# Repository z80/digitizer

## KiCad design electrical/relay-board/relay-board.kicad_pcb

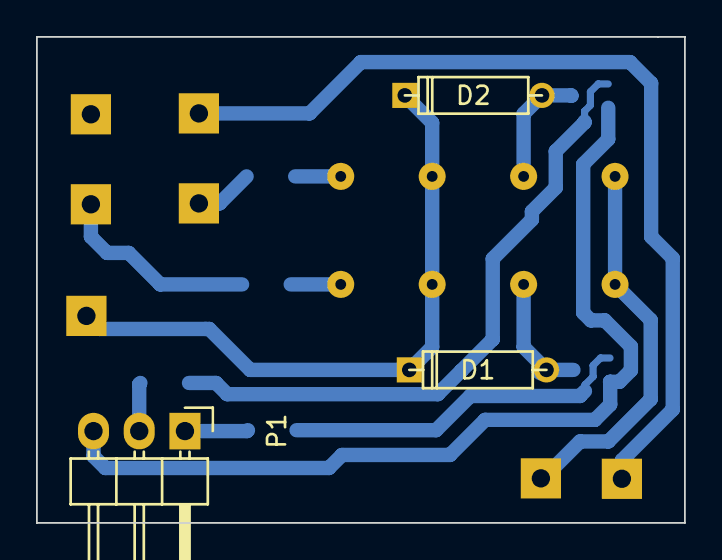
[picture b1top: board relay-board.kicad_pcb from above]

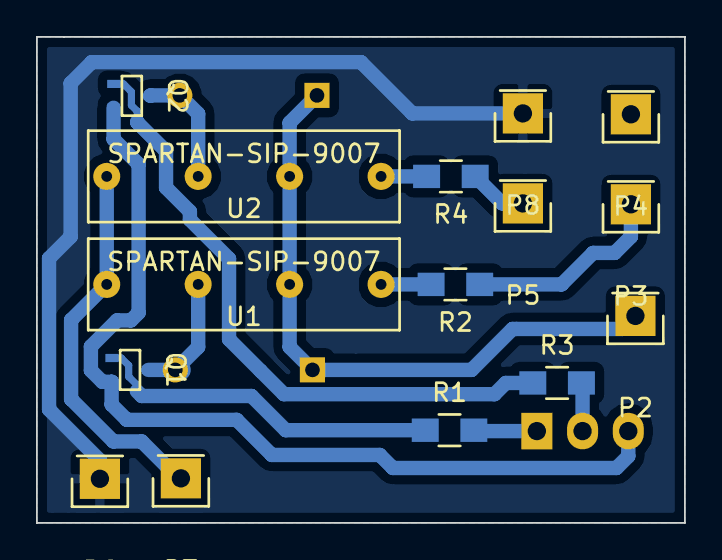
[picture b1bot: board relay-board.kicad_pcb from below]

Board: 2 copper layers, 36.0 x 27.0 mm, 18 parts (15 on the bottom side), 14 nets.

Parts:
D1, D2: 1n5819; D3
P1: CONN_01X03; Pin_Header_Angled_1x03
P2: 12V; Pin_Header_Straight_1x01
P3, P4: work; Pin_Header_Straight_1x01
P5, P6: probe; Pin_Header_Straight_1x01
P7: output; Pin_Header_Straight_1x01
P8: output gnd; Pin_Header_Straight_1x01
Q1, Q2: bc847; sot23
R1, R2, R3, R4: 1k 5%; R_0805_HandSoldering
U1, U2: SPARTAN-SIP-9007

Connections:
+12V: D1.1, D2.1, P2.1, U1.2, U2.2
/probeEn: P1.1, R1.2
/probeI: P3.1, R2.1
/workEn: P1.2, R3.2
/workI: P5.1, R4.1
GND: P1.3, Q1.3, Q2.3
GNDA: P6.1, P8.1
unnamed: D1.2, Q1.2, U1.3
unnamed: D2.2, Q2.2, U2.3
unnamed: P7.1, U1.4, U2.4
unnamed: Q1.1, R1.1
unnamed: Q2.1, R3.1
unnamed: R2.2, U1.1
unnamed: R4.2, U2.1

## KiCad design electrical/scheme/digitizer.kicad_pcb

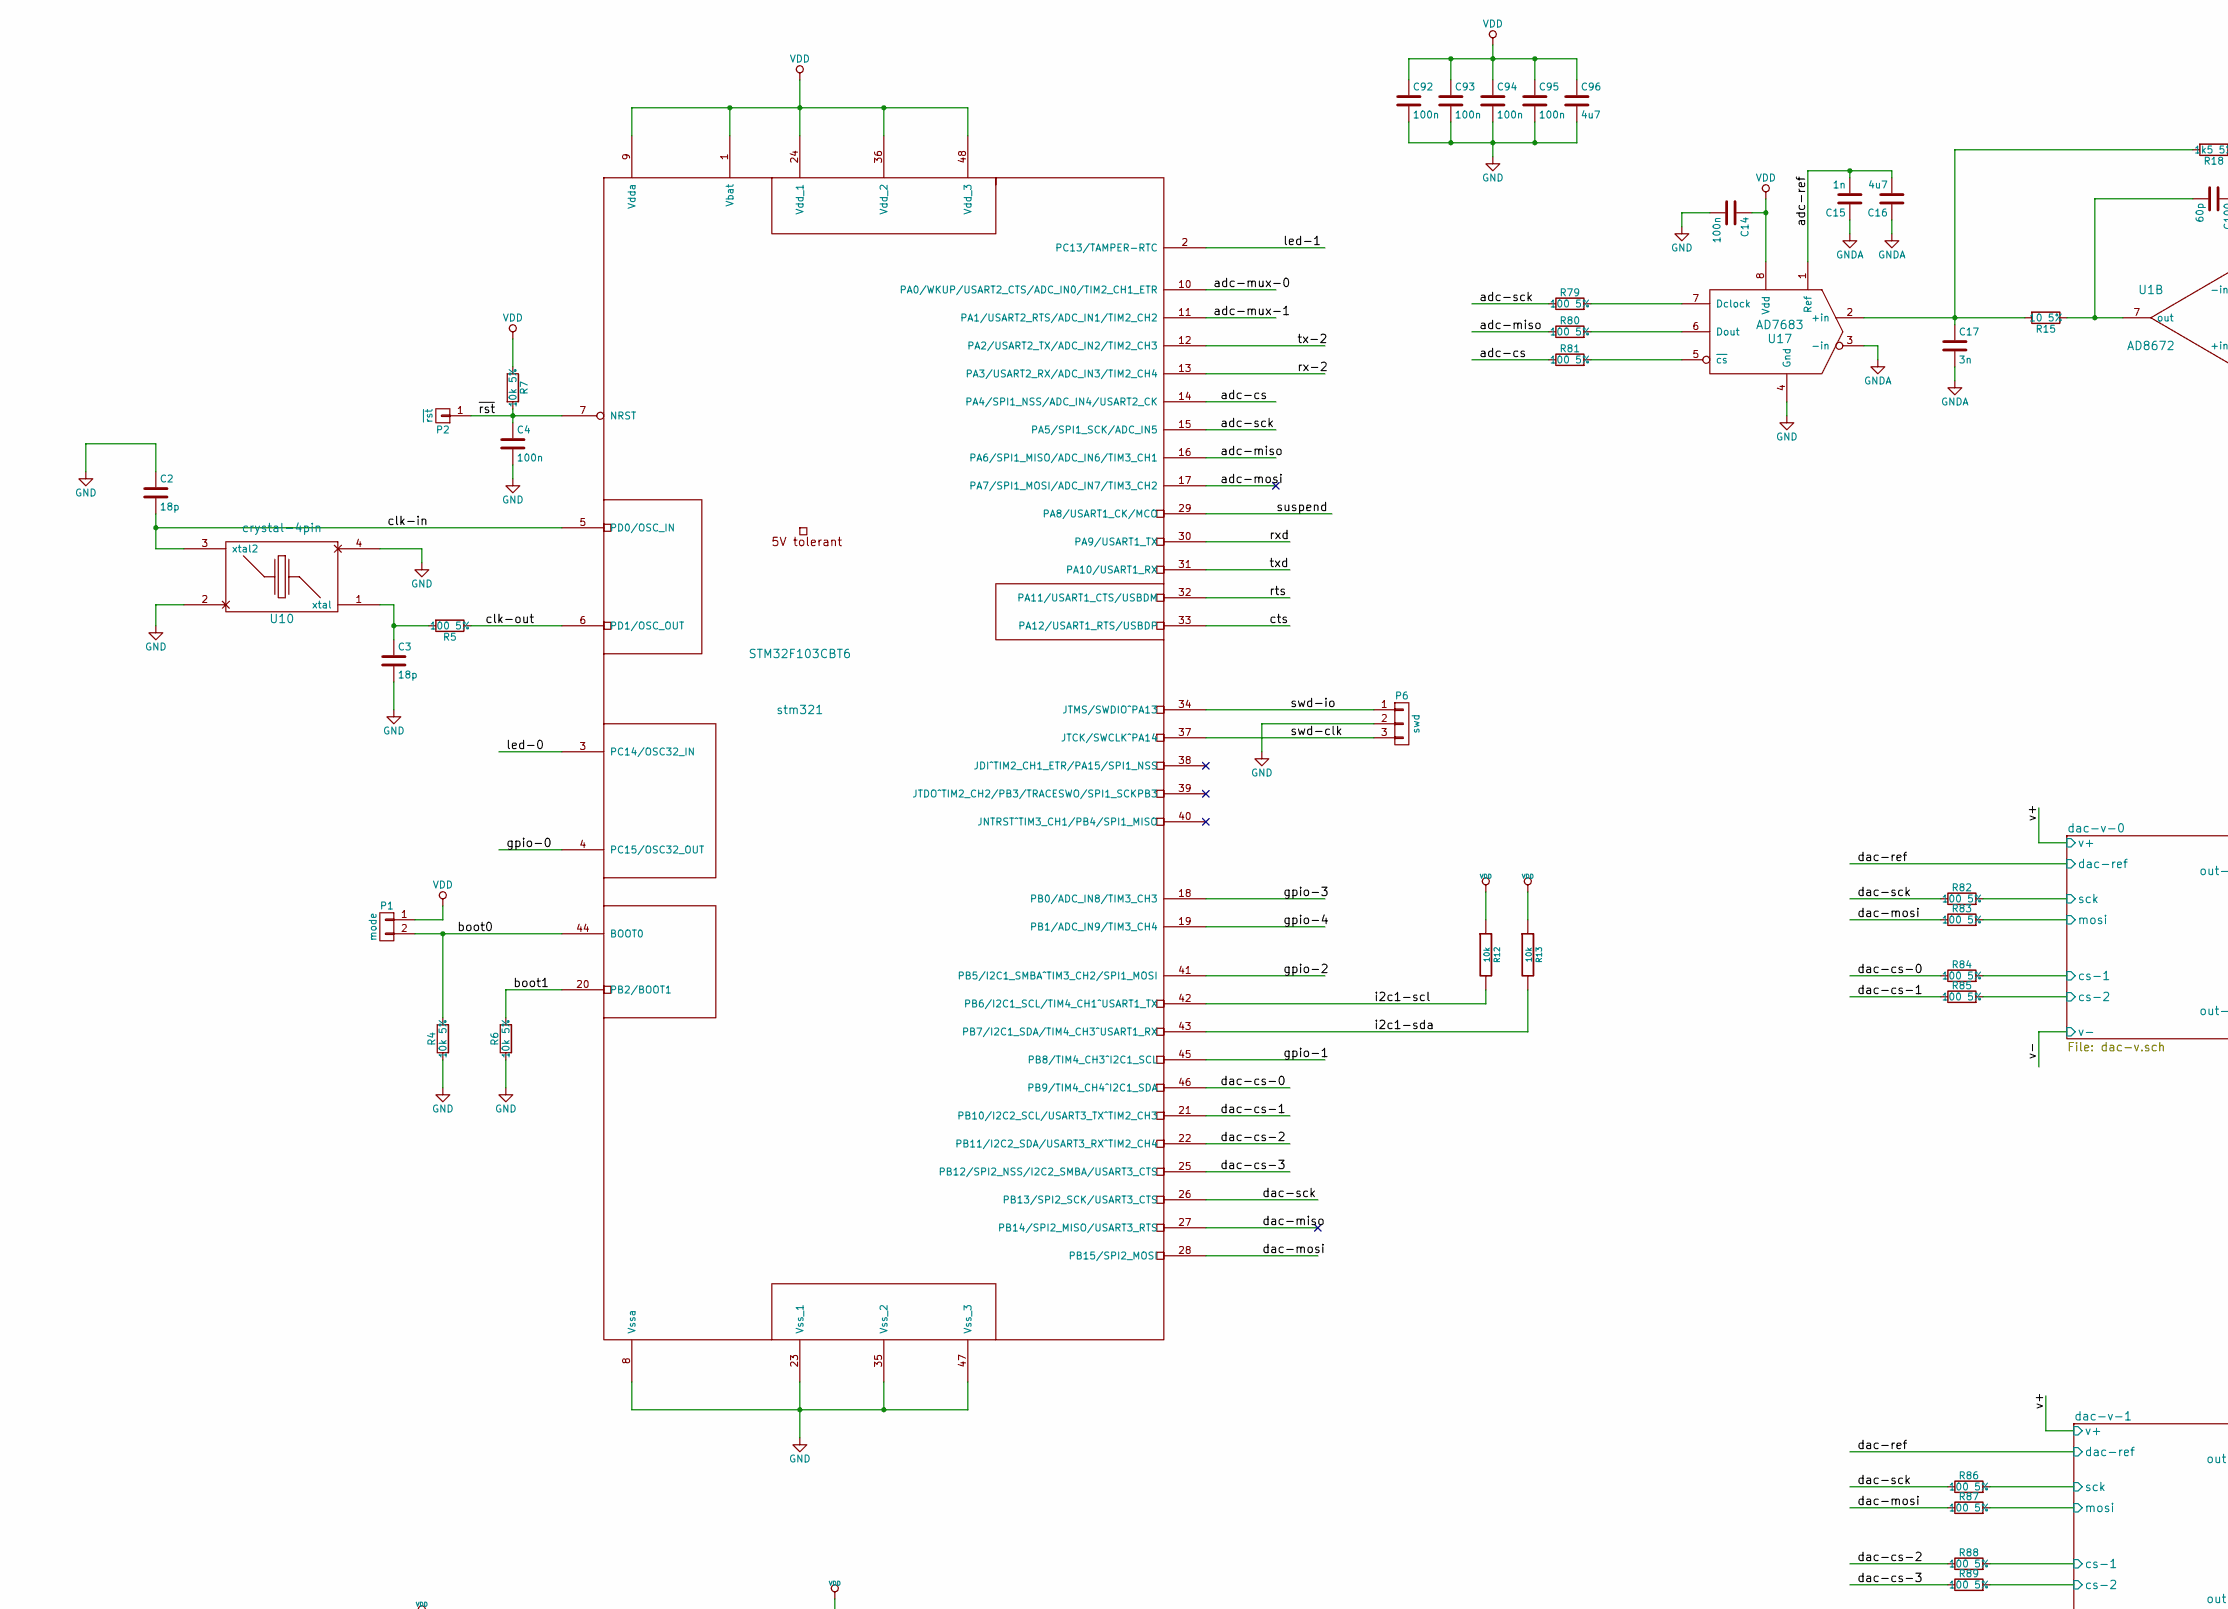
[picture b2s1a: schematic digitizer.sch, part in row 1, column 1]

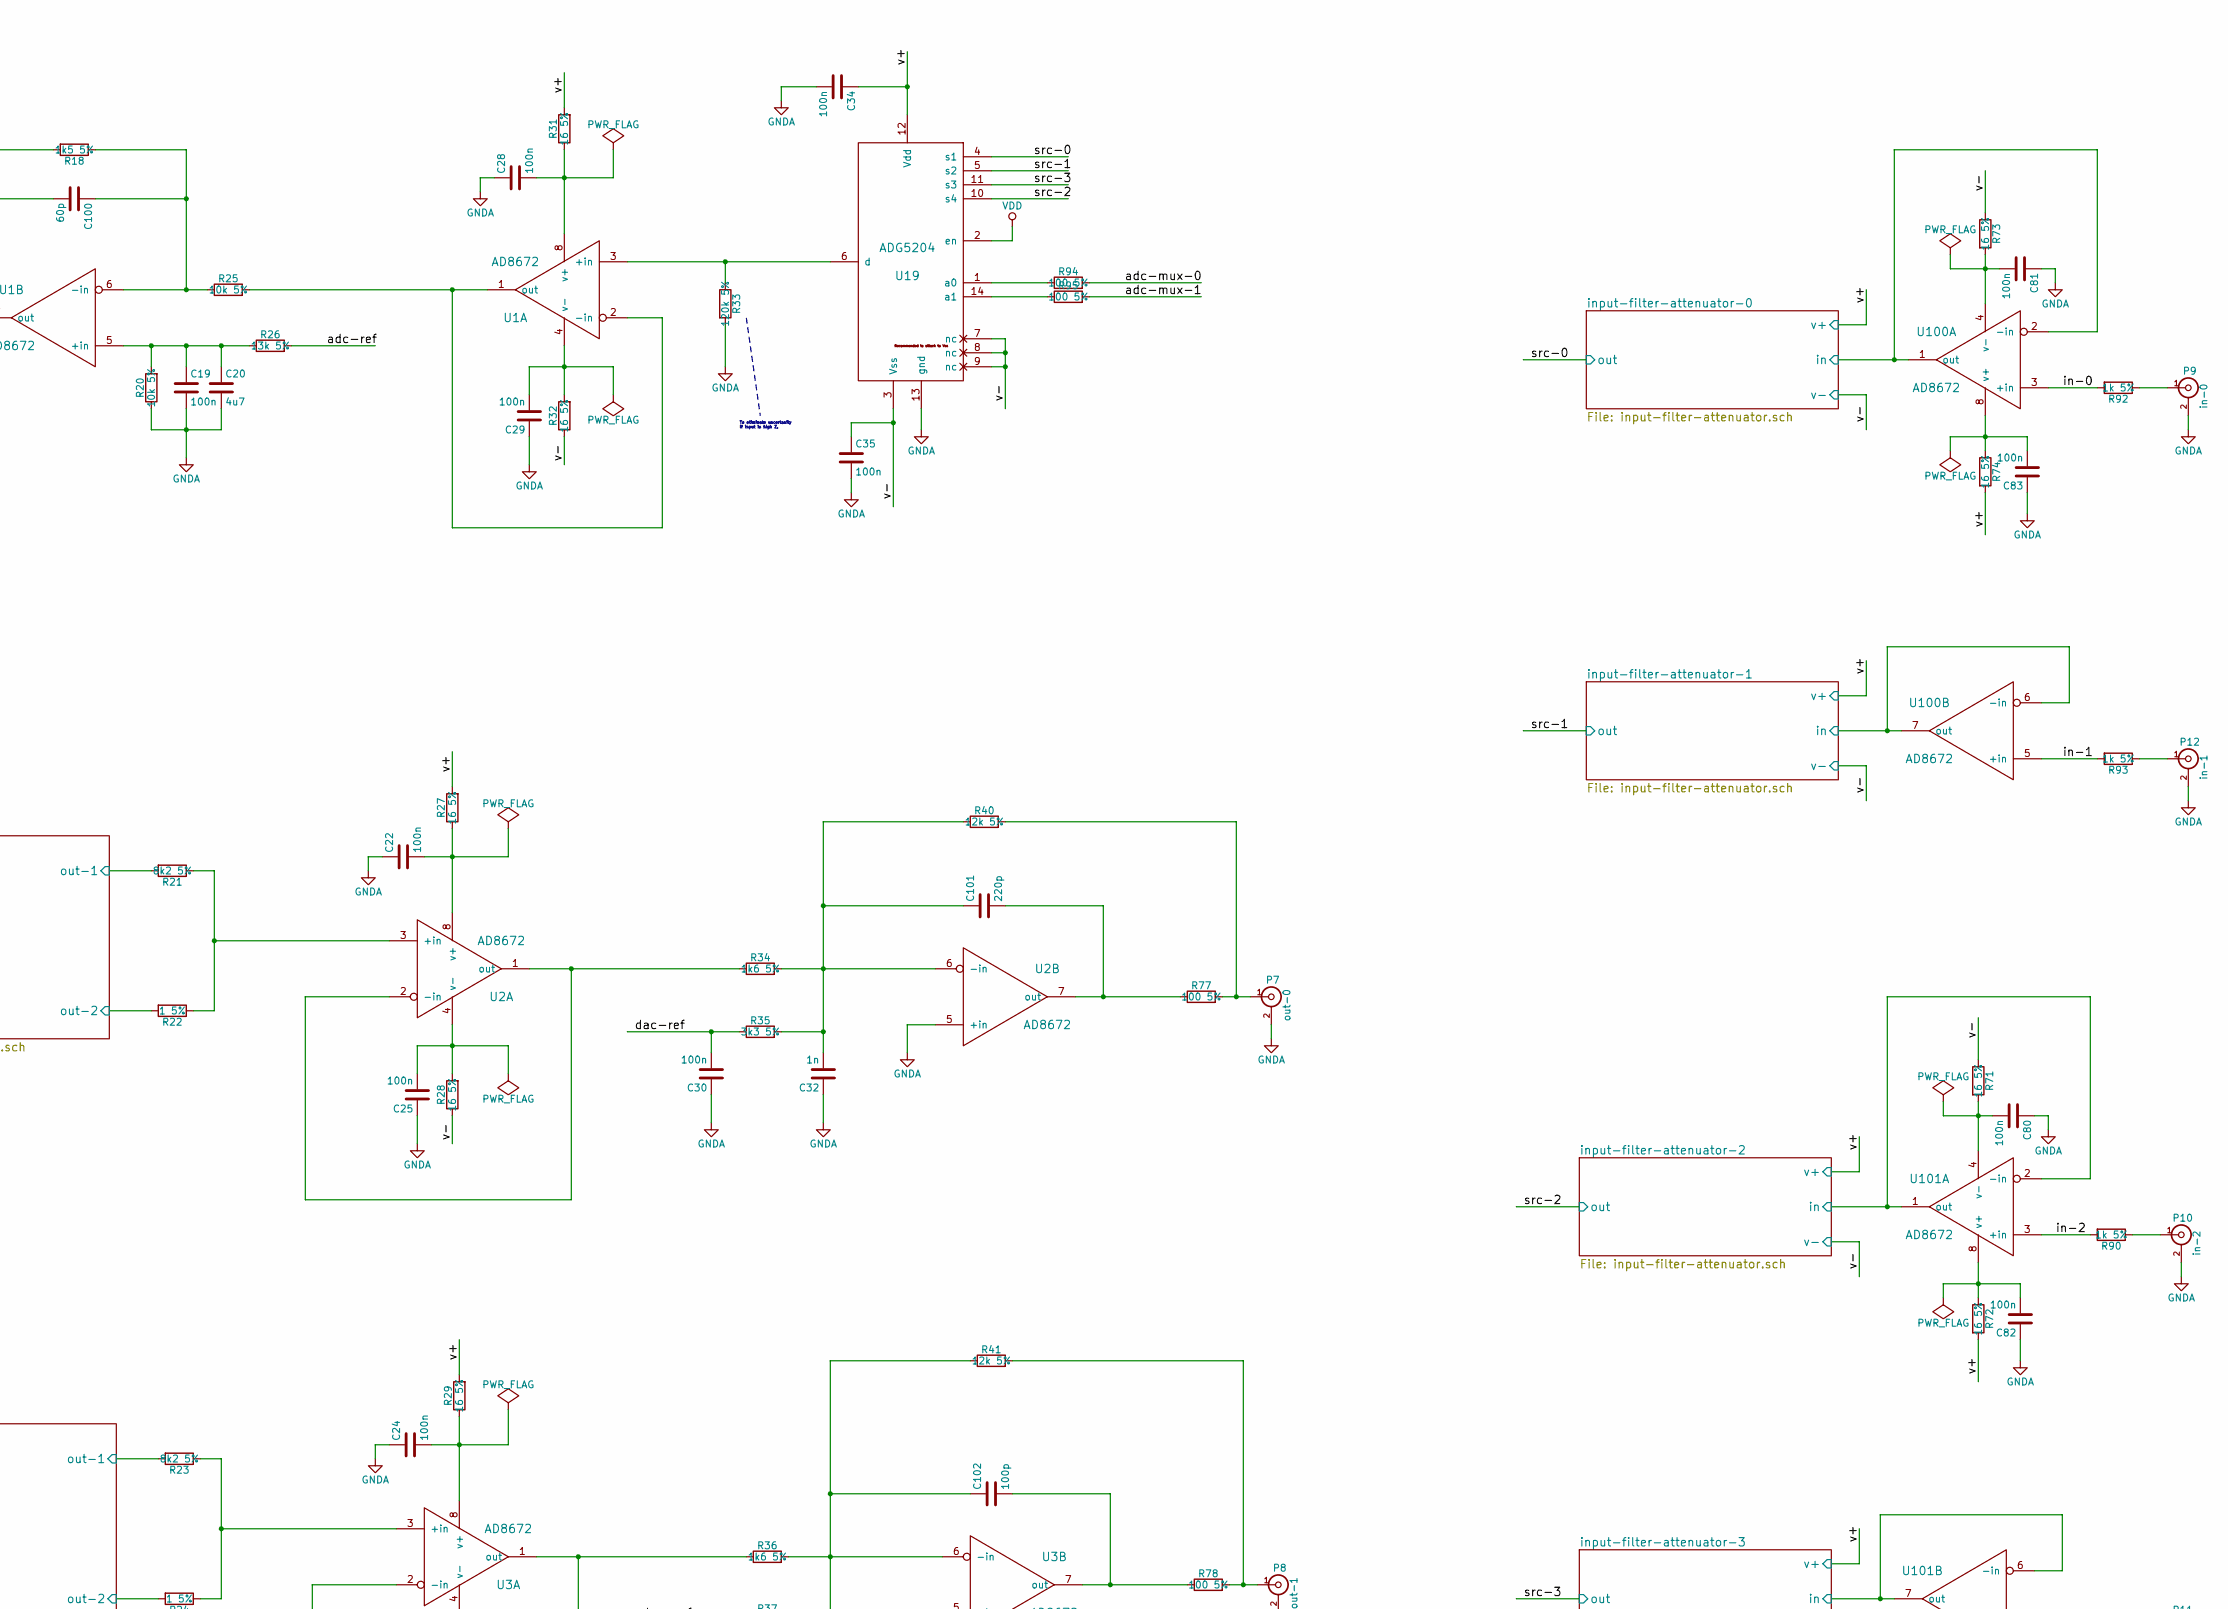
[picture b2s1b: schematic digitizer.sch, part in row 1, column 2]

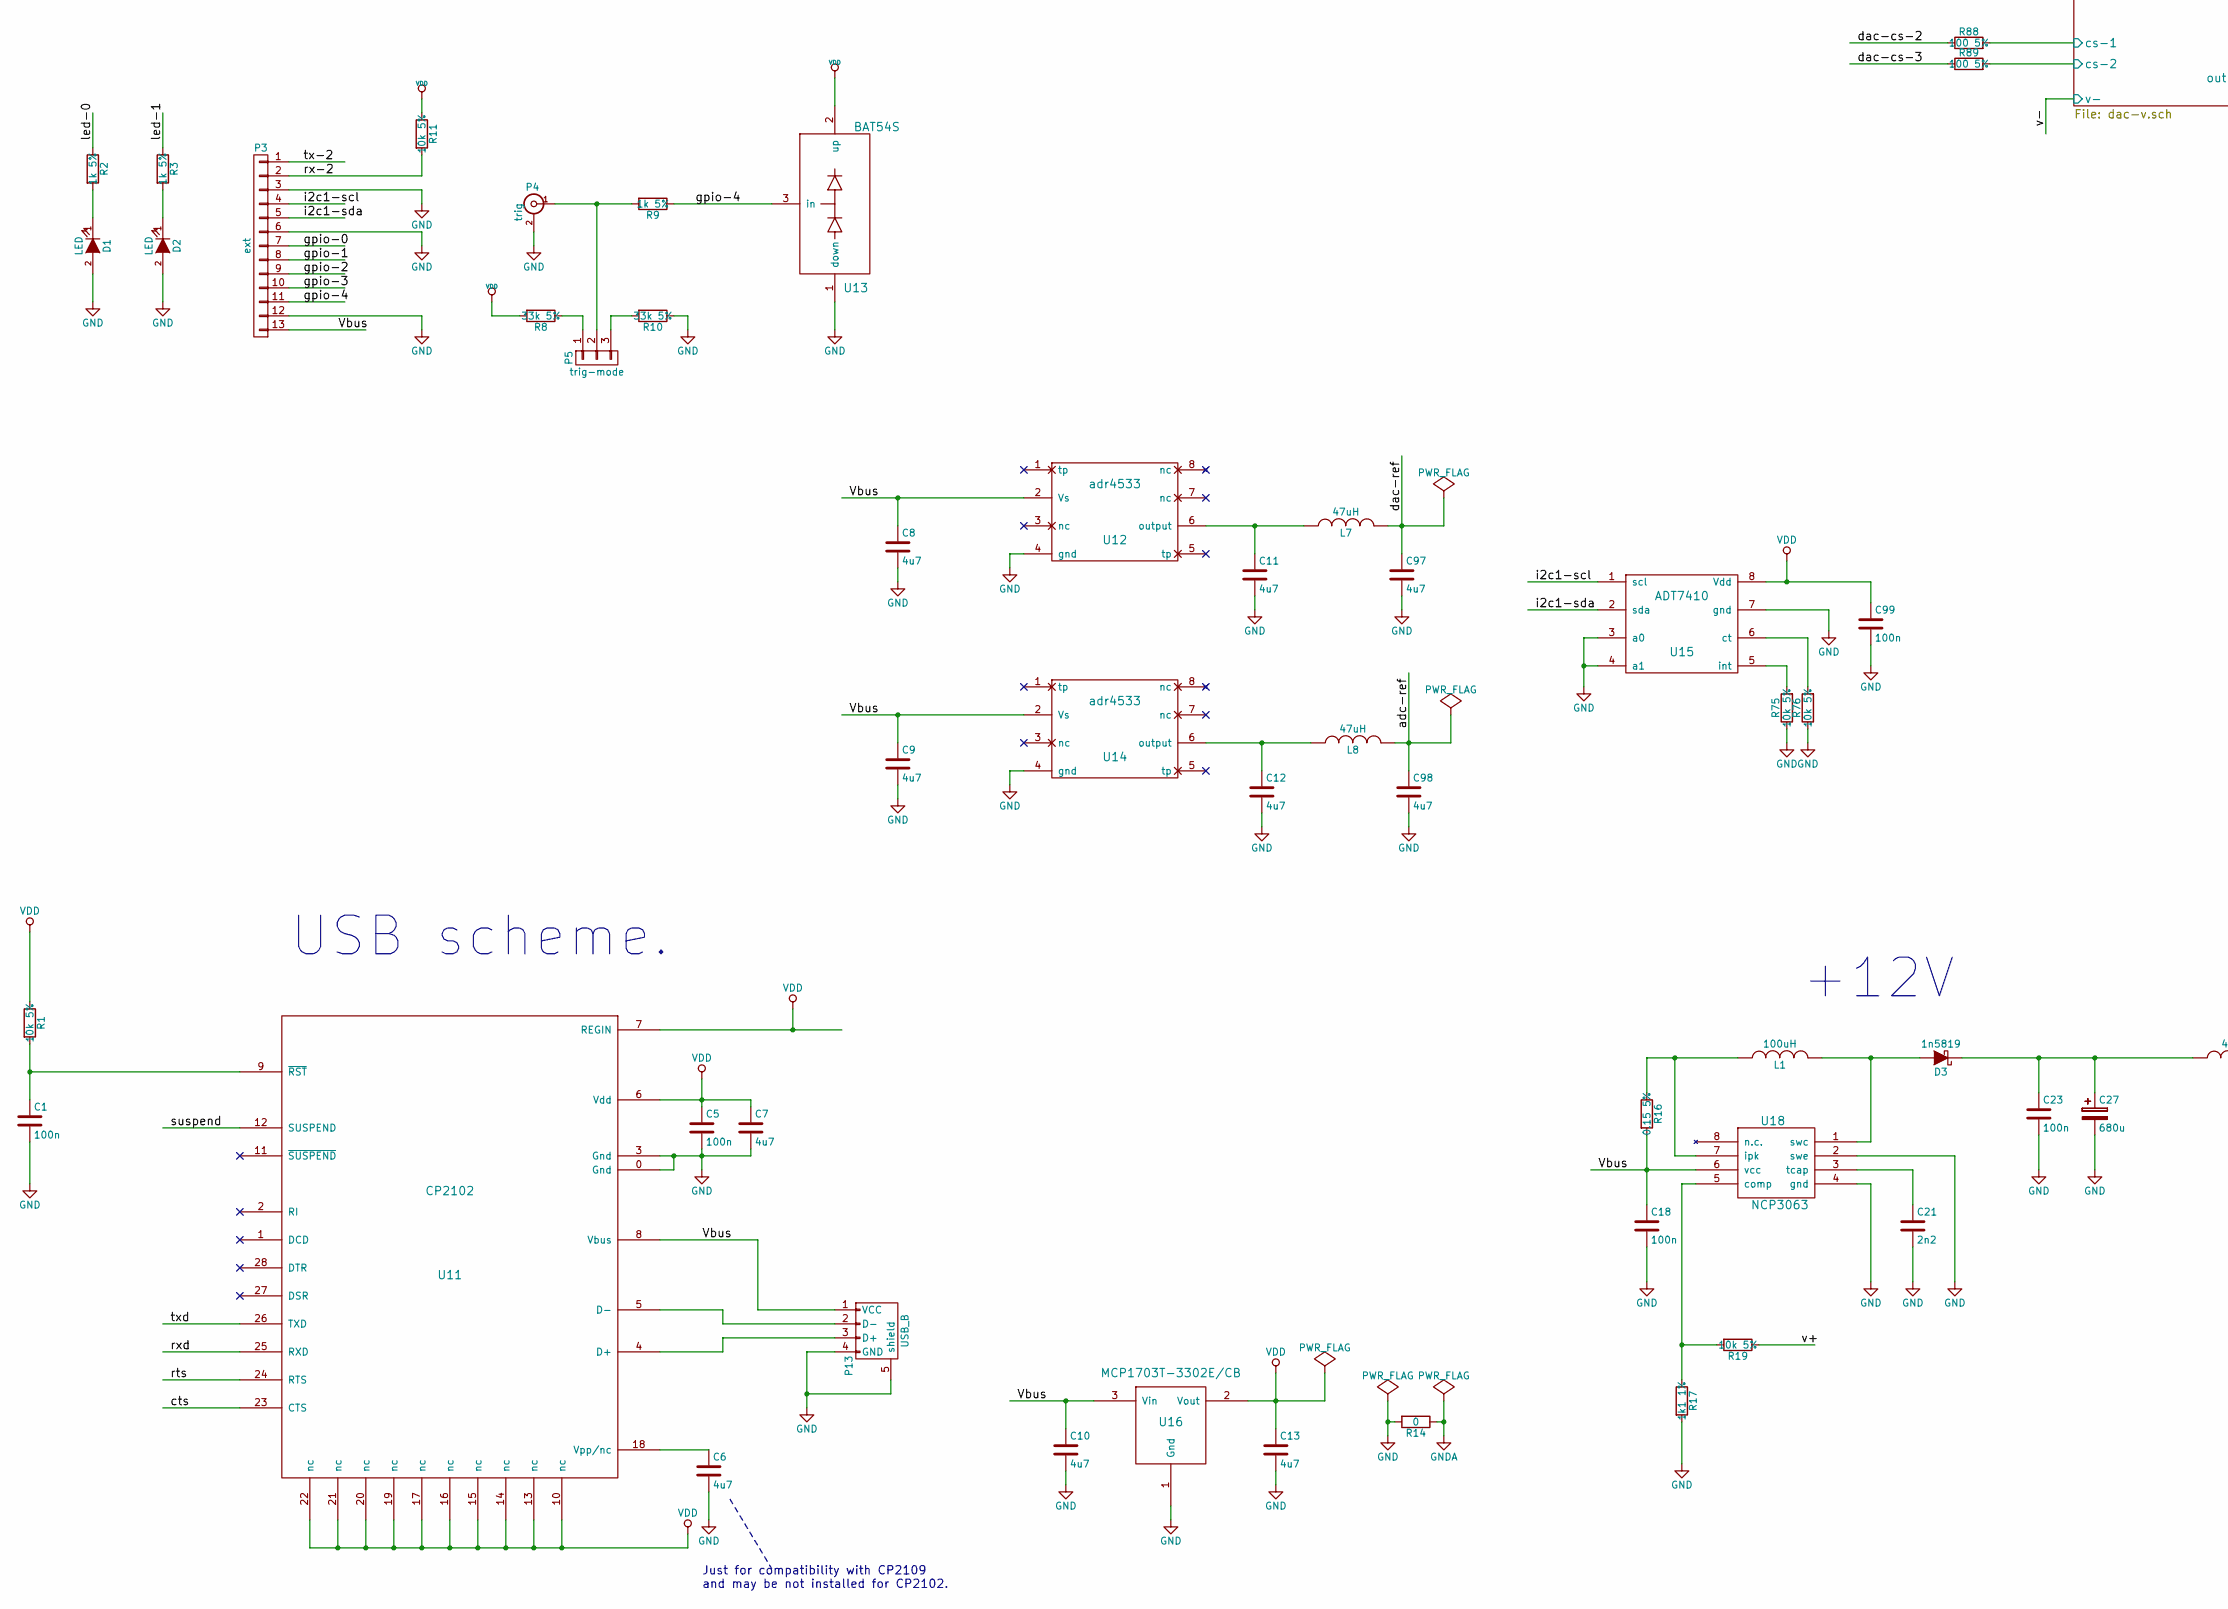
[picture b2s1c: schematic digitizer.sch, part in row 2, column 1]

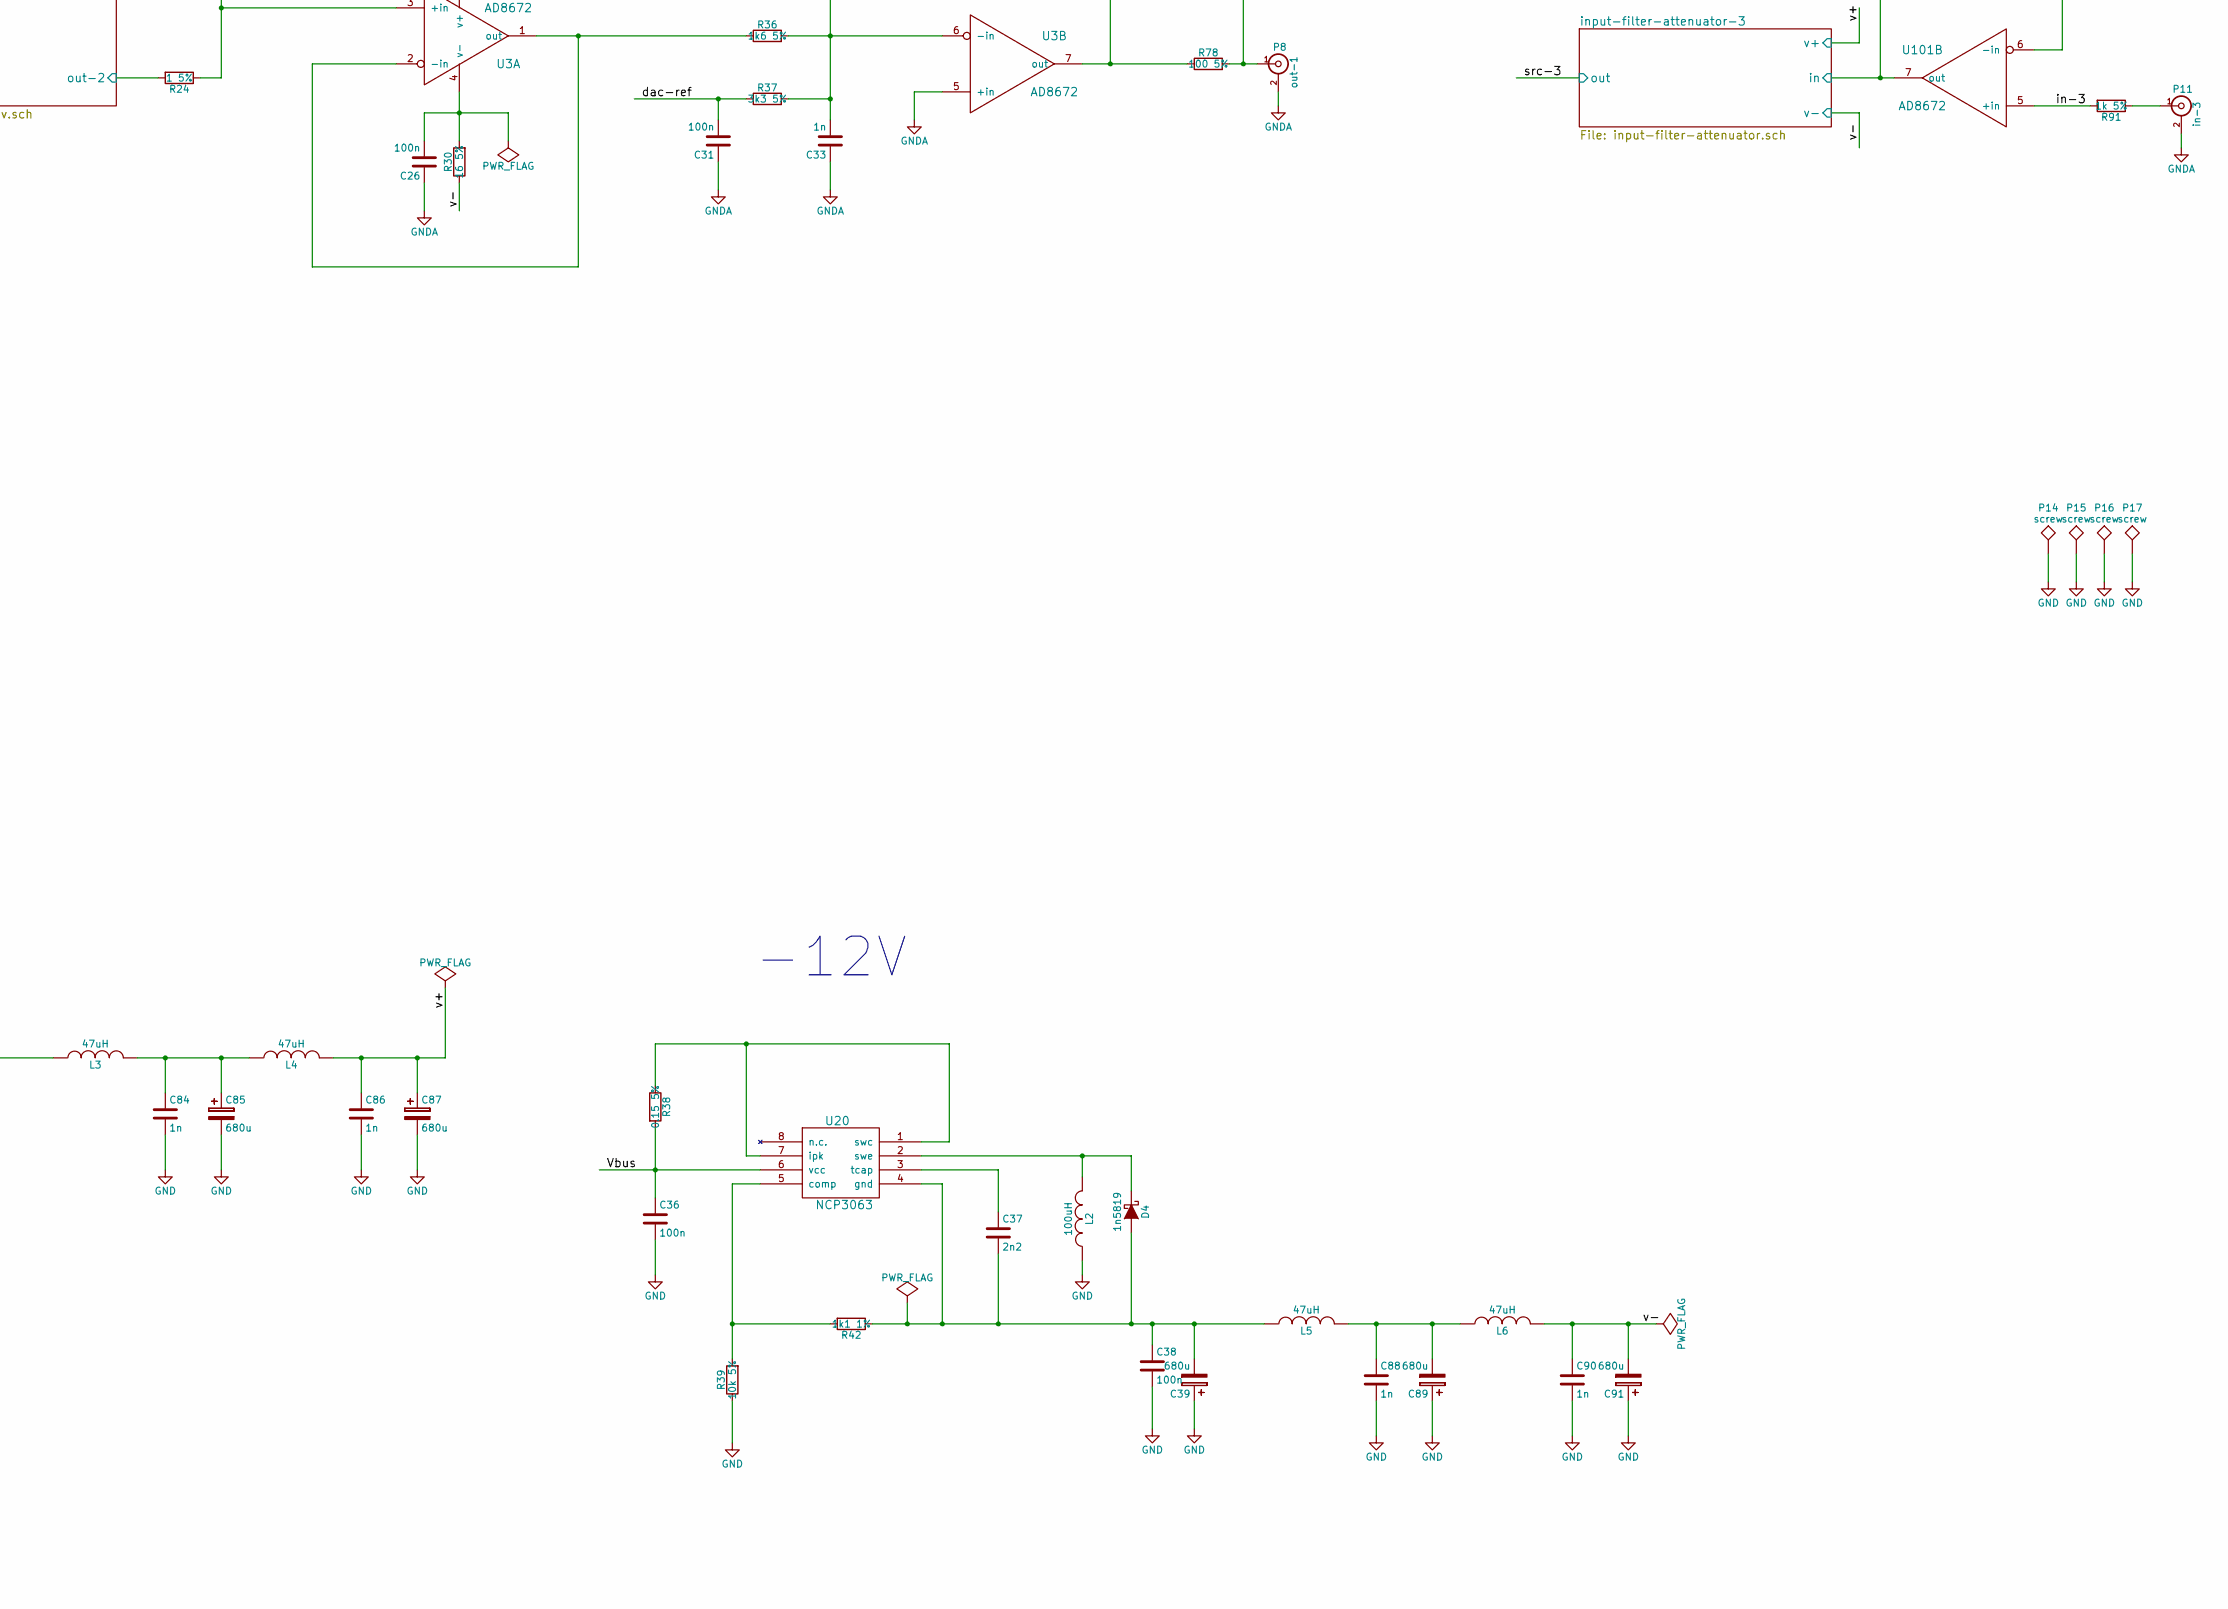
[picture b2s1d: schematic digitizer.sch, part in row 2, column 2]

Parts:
C1, C4, C5, C14, C18, C19, C22, C23, C24, C25, C26, C28, C29, C30, C31, C34, C35, C36, C38, C80, C81, C82, C83, C92, C93, C94, C95, C99: 100n; C_0805_HandSoldering
C2, C3: 18p; C_0805_HandSoldering
C6, C7, C8, C9, C10, C11, C12, C13, C16, C20, C96, C97, C98: 4u7; C_0805_HandSoldering
C15, C32, C33, C84, C86, C88, C90: 1n; C_0805_HandSoldering
C17: 3n; C_0805_HandSoldering
C21, C37: 2n2; C_0805_HandSoldering
C27, C39, C85, C87, C89, C91: 680u; C_Radial_D10_L20_P5
C100: 60p; C_0805_HandSoldering
C101: 220p; C_0805_HandSoldering
C102: 100p; C_0805_HandSoldering
D1, D2: LED; LED-3MM
D3, D4: 1n5819; Diode_DO-41_SOD81_Horizontal_RM10
L1, L2: 100uH; my_inductance
L3, L4, L5, L6, L7, L8: 47uH; C_1206_HandSoldering
P1: mode; Pin_Header_Angled_1x02
P2: ~rst~; Pin_Header_Straight_1x01
P3: ext; Socket_Strip_Angled_1x13
P4: trig; BNC_Socket_TYCO-AMP_LargePads
P5: trig-mode; Pin_Header_Angled_1x03
P6: swd; Socket_Strip_Straight_1x03
P7: out-0; BNC_Socket_TYCO-AMP_LargePads
P8: out-1; BNC_Socket_TYCO-AMP_LargePads
P9: in-0; BNC_Socket_TYCO-AMP_LargePads
P10: in-2; BNC_Socket_TYCO-AMP_LargePads
P11: in-3; BNC_Socket_TYCO-AMP_LargePads
P12: in-1; BNC_Socket_TYCO-AMP_LargePads
P13: USB_B
P14, P15, P16, P17: screw; douille_4mm
R1, R4, R6, R7, R11, R19, R20, R25, R39, R75, R76: 10k 5%; R_0805_HandSoldering
R2, R3, R9, R90, R91, R92, R93: 1k 5%; R_0805_HandSoldering
R5, R77, R78, R79, R80, R81, R82, R83, R84, R85, R86, R87, R88, R89, R94, R95: 100 5%; R_0805_HandSoldering
R8, R10: 33k 5%; R_0805_HandSoldering
R12, R13: 10k; R_0805_HandSoldering
R14: 0; R_0805_HandSoldering
R15: 10 5%; R_0805_HandSoldering
R16, R38: 0.15 5%; R_0805_HandSoldering
R17, R42: 1k1 1%; R_0805_HandSoldering
R18: 1k5 5%; R_0805_HandSoldering
R21, R23: 8k2 5%; R_0805_HandSoldering
R22, R24: 1 5%; R_0805_HandSoldering
R26: 13k 5%; R_0805_HandSoldering
R27, R28, R29, R30, R31, R32, R71, R72, R73, R74: 16 5%; R_0805_HandSoldering
R33: 120k 5%; R_0805_HandSoldering
R34, R36: 1k6 5%; R_0805_HandSoldering
R35, R37: 3k3 5%; R_0805_HandSoldering
R40, R41: 12k 5%; R_0805_HandSoldering
U1, U2, U3, U100, U101: AD8672; SOIC-8_3.9x4.9mm_Pitch1.27mm
U10: crystal-4pin; CRYSTAL-SMD-5x3
U11: CP2102
U12, U14: adr4533; SOIC-8_3.9x4.9mm_Pitch1.27mm
U13: BAT54S; SOT-23
U15: ADT7410; SOIC-8_3.9x4.9mm_Pitch1.27mm
U16: MCP1703T-3302E/CB; SOT-23
U17: AD7683; MSOP-8_3x3mm_Pitch0.65mm
U18, U20: NCP3063; SOIC-8_3.9x4.9mm_Pitch1.27mm
U19: ADG5204; TSSOP-14_4.4x5mm_Pitch0.65mm
stm321: STM32F103CBT6; LQFP48

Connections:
/Vbus: C8.1, C9.1, C10.1, C18.1, C36.1, P3.13, P13.1 (VCC), R16.2, R38.2, U11.8 (Vbus), U12.2 (Vs), U14.2 (Vs), U16.3 (Vin), U18.6 (vcc), U20.6 (vcc)
/adc-cs: R81.1, stm321.14 (PA4/SPI1_NSS/ADC_IN4/USART2_CK)
/adc-miso: R80.1, stm321.16 (PA6/SPI1_MISO/ADC_IN6/TIM3_CH1)
/adc-mux-0: R94.2, stm321.10 (PA0/WKUP/USART2_CTS/ADC_IN0/TIM2_CH1_ETR)
/adc-mux-1: R95.2, stm321.11 (PA1/USART2_RTS/ADC_IN1/TIM2_CH2)
/adc-ref: C15.2, C16.2, C98.1, L8.2, R26.2, U17.1 (Ref)
/adc-sck: R79.1, stm321.15 (PA5/SPI1_SCK/ADC_IN5)
/boot0: P1.2, R4.2, stm321.44 (BOOT0)
/boot1: R6.2, stm321.20 (PB2/BOOT1)
/clk-in: C2.2, U10.3 (xtal2), stm321.5 (PD0/OSC_IN)
/clk-out: R5.1, stm321.6 (PD1/OSC_OUT)
/cts: U11.23 (CTS), stm321.33 (PA12/USART1_RTS/USBDP)
/dac-cs-0: R84.1, stm321.46 (PB9/TIM4_CH4^I2C1_SDA)
/dac-cs-1: R85.1, stm321.21 (PB10/I2C2_SCL/USART3_TX^TIM2_CH3)
/dac-cs-2: R88.1, stm321.22 (PB11/I2C2_SDA/USART3_RX^TIM2_CH4)
/dac-cs-3: R89.1, stm321.25 (PB12/SPI2_NSS/I2C2_SMBA/USART3_CTS)
/dac-mosi: R83.1, R87.1, stm321.28 (PB15/SPI2_MOSI)
/dac-sck: R82.1, R86.1, stm321.26 (PB13/SPI2_SCK/USART3_CTS)
/dac-v-0/cs-1: R84.2; also elsewhere on the board
/dac-v-0/cs-2: R85.2; also elsewhere on the board
/dac-v-0/dac-ref: C30.2, C31.2, C97.1, L7.2, R35.1, R37.1; also elsewhere on the board
/dac-v-0/mosi: R83.2; also elsewhere on the board
/dac-v-0/out-1: R21.2; also elsewhere on the board
/dac-v-0/out-2: R22.2; also elsewhere on the board
/dac-v-0/sck: R82.2; also elsewhere on the board
/dac-v-0/v+: C34.1, C86.1, C87.1, L4.2, R19.1, R27.2, R29.2, R31.2, R72.2, R74.2, U19.12 (Vdd); also elsewhere on the board
/dac-v-0/v-: C35.1, C90.1, C91.2, L6.2, R28.1, R30.1, R32.1, R71.1, R73.1, U19.3 (Vss), U19.7 (nc), U19.8 (nc), U19.9 (nc); also elsewhere on the board
/dac-v-1/cs-1: R88.2; also elsewhere on the board
/dac-v-1/cs-2: R89.2; also elsewhere on the board
/dac-v-1/mosi: R87.2; also elsewhere on the board
/dac-v-1/out-1: R23.2; also elsewhere on the board
/dac-v-1/out-2: R24.2; also elsewhere on the board
/dac-v-1/sck: R86.2; also elsewhere on the board
/gpio-0: P3.7, stm321.4 (PC15/OSC32_OUT)
/gpio-1: P3.8, stm321.45 (PB8/TIM4_CH3^I2C1_SCL)
/gpio-2: P3.9, stm321.41 (PB5/I2C1_SMBA^TIM3_CH2/SPI1_MOSI)
/gpio-3: P3.10, stm321.18 (PB0/ADC_IN8/TIM3_CH3)
/gpio-4: P3.11, R9.1, U13.3 (in), stm321.19 (PB1/ADC_IN9/TIM3_CH4)
/i2c1-scl: P3.4, R12.2, U15.1 (scl), stm321.42 (PB6/I2C1_SCL/TIM4_CH1^USART1_TX)
/i2c1-sda: P3.5, R13.2, U15.2 (sda), stm321.43 (PB7/I2C1_SDA/TIM4_CH3^USART1_RX)
/in-0: R92.2, U100.3 (+in)
/in-1: R93.2, U100.5 (+in)
/in-2: R90.2, U101.3 (+in)
/in-3: R91.2, U101.5 (+in)
/input-filter-attenuator-0/in: U100.1 (out), U100.2 (-in); also elsewhere on the board
/input-filter-attenuator-0/out: U19.4 (s1); also elsewhere on the board
/input-filter-attenuator-1/in: U100.6 (-in), U100.7 (out); also elsewhere on the board
/input-filter-attenuator-1/out: U19.5 (s2); also elsewhere on the board
/input-filter-attenuator-2/in: U101.1 (out), U101.2 (-in); also elsewhere on the board
/input-filter-attenuator-2/out: U19.10 (s4); also elsewhere on the board
/input-filter-attenuator-3/in: U101.6 (-in), U101.7 (out); also elsewhere on the board
/input-filter-attenuator-3/out: U19.11 (s3); also elsewhere on the board
/led-0: R2.1, stm321.3 (PC14/OSC32_IN)
/led-1: R3.1, stm321.2 (PC13/TAMPER-RTC)
/rts: U11.24 (RTS), stm321.32 (PA11/USART1_CTS/USBDM)
/rx-2: P3.2, R11.2, stm321.13 (PA3/USART2_RX/ADC_IN3/TIM2_CH4)
/rxd: U11.25 (RXD), stm321.30 (PA9/USART1_TX)
/suspend: U11.12 (SUSPEND), stm321.29 (PA8/USART1_CK/MCO)
/swd-clk: P6.3, stm321.37 (JTCK/SWCLK^PA14)
/swd-io: P6.1, stm321.34 (JTMS/SWDIO^PA13)
/tx-2: P3.1, stm321.12 (PA2/USART2_TX/ADC_IN2/TIM2_CH3)
/txd: U11.26 (TXD), stm321.31 (PA10/USART1_RX)
/~rst~: C4.1, P2.1, R7.2, stm321.7 (NRST)
GND: C1.2, C2.1, C3.2, C4.2, C5.2, C6.2, C7.2, C8.2, C9.2, C10.2, C11.2, C12.2, C13.2, C14.2, C18.2, C21.2, C23.2, C27.2, C36.2, C38.2, C39.1, C84.2, C85.2, C86.2, C87.2, C88.2, C89.1, C90.2, C91.1, C92.2, C93.2, C94.2, C95.2, C96.2, C97.2, C98.2, C99.2, D1.2 (A), D2.2 (A), L2.1, P3.3, P3.6, P3.12, P4.2 (Ext), P6.2, P13.4 (GND), P13.5 (shield), P14.1, P15.1, P16.1, P17.1, R4.1, R6.1, R10.1, R14.2, R17.2, R39.1, R75.1, R76.1, U10.2, U10.4, U11.0 (Gnd), U11.3 (Gnd), U12.4 (gnd), U13.1 (down), U14.4 (gnd), U15.3 (a0), U15.4 (a1), U15.7 (gnd), U16.1 (Gnd), U17.4 (Gnd), U18.2 (swe), U18.4 (gnd), stm321.8 (Vssa), stm321.23 (Vss_1), stm321.35 (Vss_2), stm321.47 (Vss_3); also elsewhere on the board
GNDA: C15.1, C16.1, C17.2, C19.2, C20.2, C22.1, C24.1, C25.1, C26.1, C28.1, C29.1, C30.1, C31.1, C32.1, C33.1, C34.2, C35.2, C80.1, C81.1, C82.1, C83.1, P7.2 (Ext), P8.2 (Ext), P9.2 (Ext), P10.2 (Ext), P11.2 (Ext), P12.2 (Ext), R14.1, R20.1, R33.2, U2.5 (+in), U3.5 (+in), U17.3 (-in), U19.13 (gnd); also elsewhere on the board
unnamed: C1.1, R1.2, U11.9 (~RST~)
unnamed: C3.1, R5.2, U10.1 (xtal)
unnamed: C6.1, U11.18 (Vpp/nc)
unnamed: C11.1, L7.1, U12.6 (output)
unnamed: C12.1, L8.1, U14.6 (output)
unnamed: C17.1, R15.2, R18.2, U17.2 (+in)
unnamed: C19.1, C20.1, R20.2, R26.1, U1.5 (+in)
unnamed: C21.1, U18.3 (tcap)
unnamed: C22.2, R27.1, U2.8 (v+)
unnamed: C23.1, C27.1, D3.1 (K), L3.1
unnamed: C24.2, R29.1, U3.8 (v+)
unnamed: C25.2, R28.2, U2.4 (v-)
unnamed: C26.2, R30.2, U3.4 (v-)
unnamed: C28.2, R31.1, U1.8 (v+)
unnamed: C29.2, R32.2, U1.4 (v-)
unnamed: C37.1, U20.3 (tcap)
unnamed: C37.2, C38.1, C39.2, D4.2 (A), L5.1, R42.1, U20.4 (gnd)
unnamed: C80.2, R71.2, U101.4 (v-)
unnamed: C81.2, R73.2, U100.4 (v-)
unnamed: C82.2, R72.1, U101.8 (v+)
unnamed: C83.2, R74.1, U100.8 (v+)
unnamed: C84.1, C85.1, L3.2, L4.1
unnamed: C88.1, C89.2, L5.2, L6.1
unnamed: C100.1, R18.1, R25.1, U1.6 (-in)
unnamed: C100.2, R15.1, U1.7 (out)
unnamed: C32.2, C101.1, R34.2, R35.2, R40.1, U2.6 (-in)
unnamed: C101.2, R77.1, U2.7 (out)
unnamed: C33.2, C102.1, R36.2, R37.2, R41.1, U3.6 (-in)
unnamed: C102.2, R78.1, U3.7 (out)
unnamed: D1.1 (K), R2.2
unnamed: D2.1 (K), R3.2
unnamed: D3.2 (A), L1.2, U18.1 (swc)
unnamed: D4.1 (K), L2.2, U20.2 (swe)
unnamed: L1.1, R16.1, U18.7 (ipk)
unnamed: P4.1 (In), P5.2, R9.2
unnamed: P5.1, R8.1
unnamed: P5.3, R10.2
unnamed: P7.1 (In), R40.2, R77.2
unnamed: P8.1 (In), R41.2, R78.2
unnamed: P9.1 (In), R92.1
unnamed: P10.1 (In), R90.1
unnamed: P11.1 (In), R91.1
unnamed: P12.1 (In), R93.1
unnamed: P13.2 (D-), U11.5 (D-)
unnamed: P13.3 (D+), U11.4 (D+)
unnamed: R17.1, R19.2, U18.5 (comp)
unnamed: R21.1, R22.1, U2.3 (+in)
unnamed: R23.1, R24.1, U3.3 (+in)
unnamed: R25.2, U1.1 (out), U1.2 (-in)
unnamed: R33.1, U1.3 (+in), U19.6 (d)
unnamed: R34.1, U2.1 (out), U2.2 (-in)
unnamed: R36.1, U3.1 (out), U3.2 (-in)
unnamed: R38.1, U20.1 (swc), U20.7 (ipk)
unnamed: R39.2, R42.2, U20.5 (comp)
unnamed: R75.2, U15.5 (int)
unnamed: R76.2, U15.6 (ct)
unnamed: R79.2, U17.7 (Dclock)
unnamed: R80.2, U17.6 (Dout)
unnamed: R81.2, U17.5 (~cs~)
unnamed: R94.1, U19.1 (a0)
unnamed: R95.1, U19.14 (a1)
VDD: C5.1, C7.1, C13.1, C14.1, C92.1, C93.1, C94.1, C95.1, C96.1, C99.1, P1.1, R1.1, R7.1, R8.2, R11.1, R12.1, R13.1, U11.6 (Vdd), U11.7 (REGIN), U11.10 (nc), U11.13 (nc), U11.14 (nc), U11.15 (nc), U11.16 (nc), U11.17 (nc), U11.19 (nc), U11.20 (nc), U11.21 (nc), U11.22 (nc), U13.2 (up), U15.8 (Vdd), U16.2 (Vout), U17.8 (Vdd), U19.2 (en), stm321.1 (Vbat), stm321.9 (Vdda), stm321.24 (Vdd_1), stm321.36 (Vdd_2), stm321.48 (Vdd_3); also elsewhere on the board

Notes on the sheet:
+12V
-12V
Just for compatibility with CP2109 and may be not installed for CP2102.
USB scheme.
To eliminate uncertanity if input is high Z.
